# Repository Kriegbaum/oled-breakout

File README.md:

# oled-breakout
Breakout board for Crystalfontz 128x128 Oled display

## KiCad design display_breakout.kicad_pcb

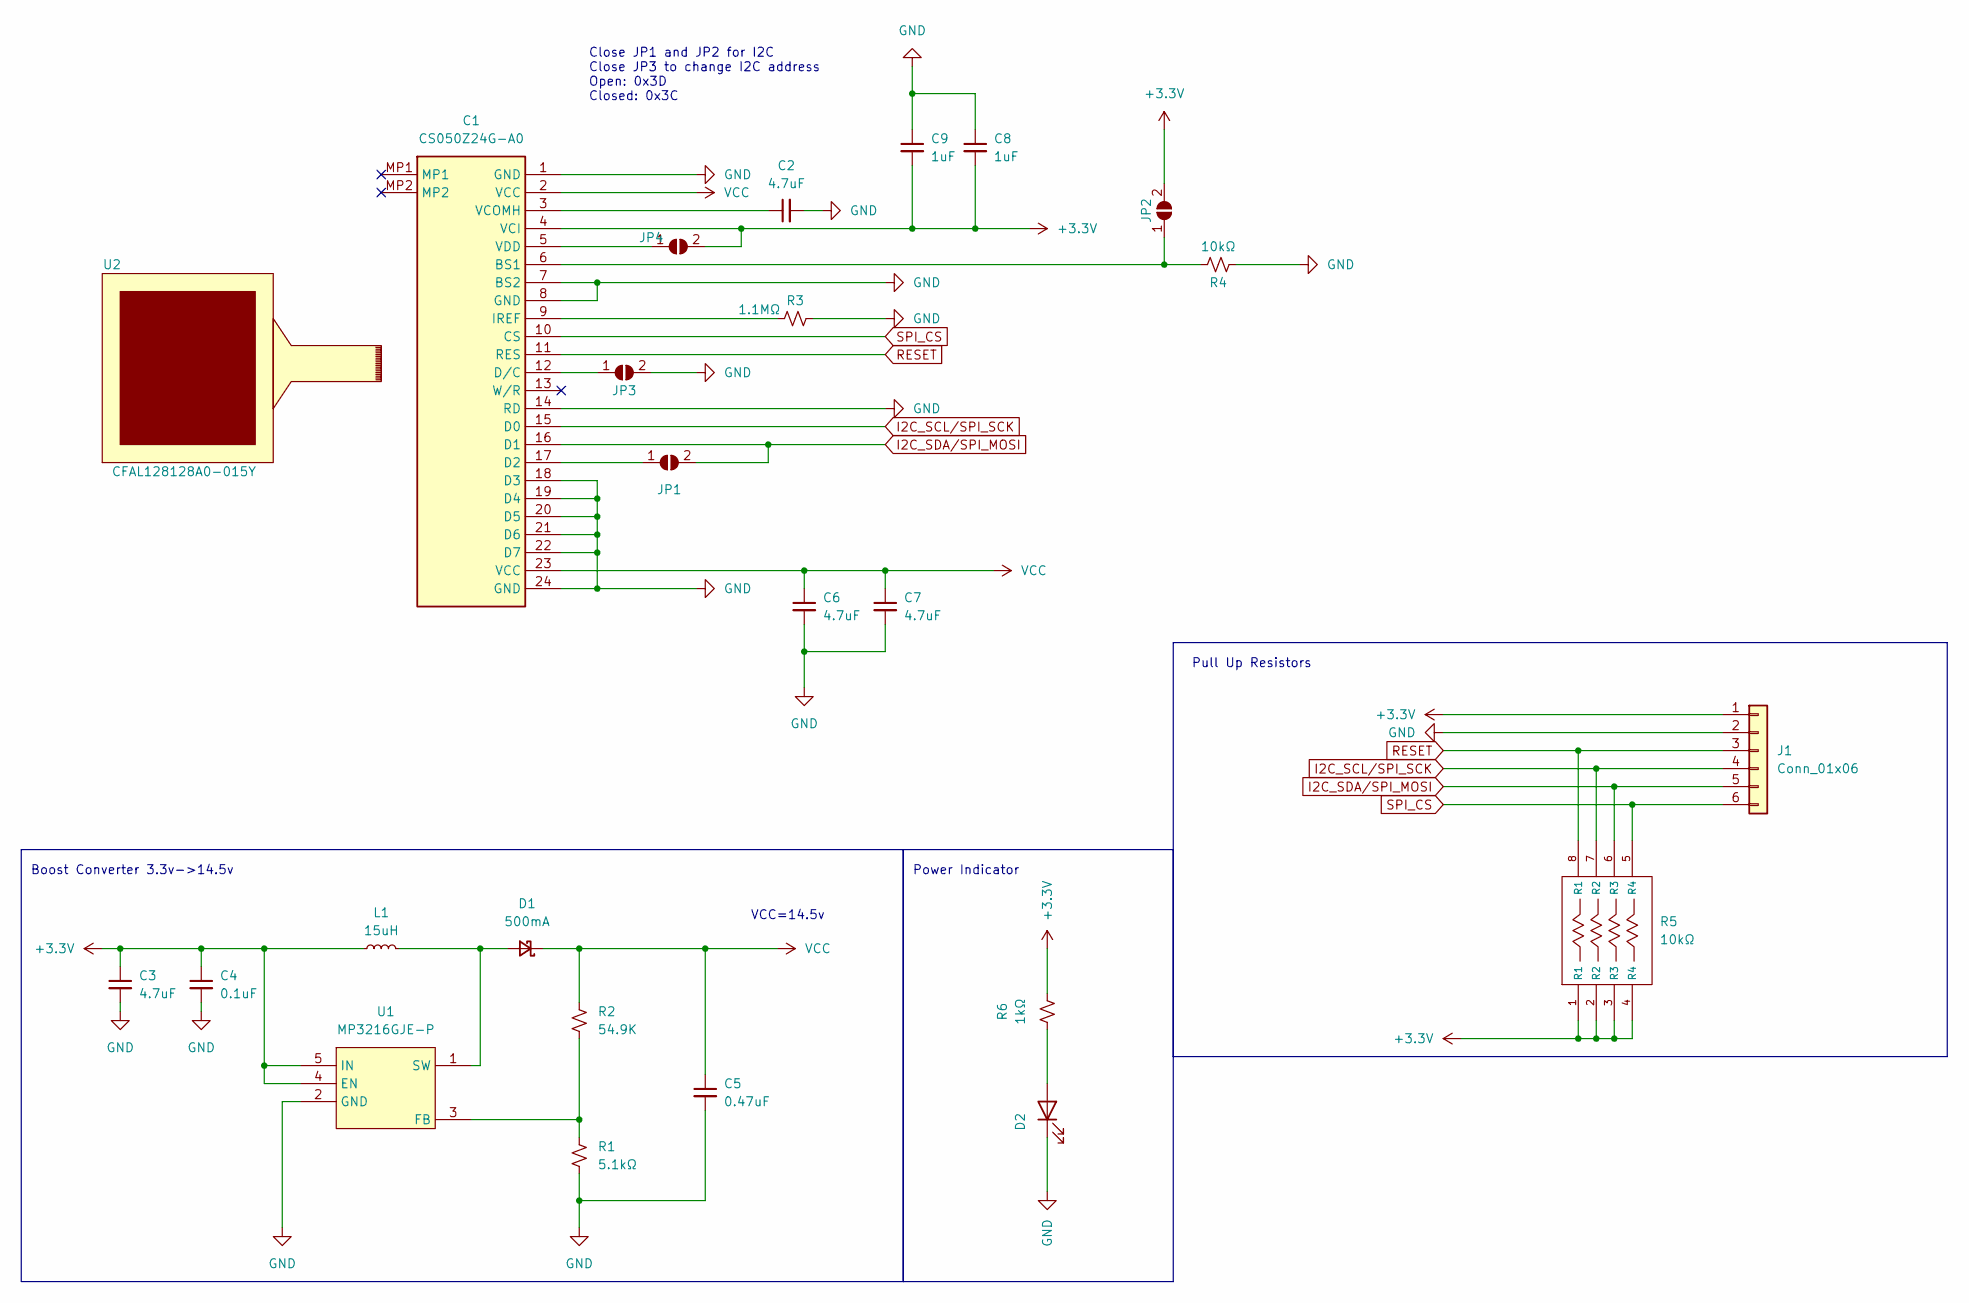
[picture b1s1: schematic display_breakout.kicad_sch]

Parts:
C1: CS050Z24G-A0; CS050Z24GA0; Manufacturer_Part_Number CS050Z24G-A0
C2, C3, C6, C7: CL21A475KAQNNNE; 0805_cap; Tolerance 10%; Voltage 25v
C4: CL21B104KBCNNNC; 0805_cap; Tolerance 10%; Voltage 50v
C5: UMK212B7474KG-T; 0805_cap; Tolerance 10%; Voltage 50v
C8, C9: CL21B105KBFNNNG; 0805_cap; Tolerance 10%; Voltage 50v
D1: B0540WS-TP; D_SOD-323_HandSoldering; Voltage 40V
D2: QBLP615-R; LED_1206_3216Metric_Pad1.42x1.75mm_HandSolder
J1: Conn_01x06; PinHeader_1x06_P2.54mm_Vertical
JP1, JP2, JP3, JP4: SolderJumper_2_Open; SolderJumper-2_P1.3mm_Open_RoundedPad1.0x1.5mm
L1: SDEM25201B-150MS; L_1008_2520Metric_Pad1.43x2.20mm_HandSolder
R1: RC0805FR-075K1L; R_0805_2012Metric_Pad1.20x1.40mm_HandSolder
R2: RC0805FR-0754K9L; R_0805_2012Metric_Pad1.20x1.40mm_HandSolder
R3: RC0805FR-071M1L; R_0805_2012Metric_Pad1.20x1.40mm_HandSolder
R4: RC0805JR-0710KL; R_0805_2012Metric_Pad1.20x1.40mm_HandSolder
R5: YC124-JR-0710KL; Resistor_Array_0805_x4
R6: RNCP0805FTD1K00; R_0805_2012Metric_Pad1.20x1.40mm_HandSolder
U1: MP3216GJE-P; SOT-23-5; Input voltage 2.5-6v; Output voltage 0-36v
U2: CFAL128128A0-015Y; CFAL128128A0-015

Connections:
+3.3V: C1.4 (VCI), C3.1, C4.1, C8.2, C9.2, J1.1, JP2.2 (B), JP4.2 (B), L1.1, R5.1 (R1), R5.2 (R2), R5.3 (R3), R5.4 (R4), R6.2, U1.4 (EN), U1.5 (IN)
GND: C1.1 (GND), C1.7 (BS2), C1.8 (GND), C1.14 (RD), C1.18 (D3), C1.19 (D4), C1.20 (D5), C1.21 (D6), C1.22 (D7), C1.24 (GND), C2.2, C3.2, C4.2, C5.2, C6.2, C7.2, C8.1, C9.1, D2.1 (K), J1.2, JP3.2 (B), R1.2, R3.2, R4.1, U1.2 (GND)
I2C_SCL/SPI_SCK: C1.15 (D0), J1.4, R5.7 (R2)
I2C_SDA/SPI_MOSI: C1.16 (D1), J1.5, JP1.2 (B), R5.6 (R3)
unnamed: C1.6 (BS1), JP2.1 (A), R4.2
unnamed: C1.17 (D2), JP1.1 (A)
unnamed: C1.12 (D/C), JP3.1 (A)
unnamed: C1.9 (IREF), R3.1
unnamed: C1.3 (VCOMH), C2.1
unnamed: C1.5 (VDD), JP4.1 (A)
unnamed: D1.2 (A), L1.2, U1.1 (SW)
unnamed: D2.2 (A), R6.1
unnamed: R1.1, R2.2, U1.3 (FB)
RESET: C1.11 (RES), J1.3, R5.8 (R1)
SPI_CS: C1.10 (CS), J1.6, R5.5 (R4)
VCC: C1.2 (VCC), C1.23 (VCC), C5.1, C6.1, C7.1, D1.1 (K), R2.1

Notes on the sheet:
Boost Converter 3.3v->14.5v
VCC=14.5v
Close JP1 and JP2 for I2C Close JP3 to change I2C address Open: 0x3D Closed: 0x3C
Pull Up Resistors
Power Indicator

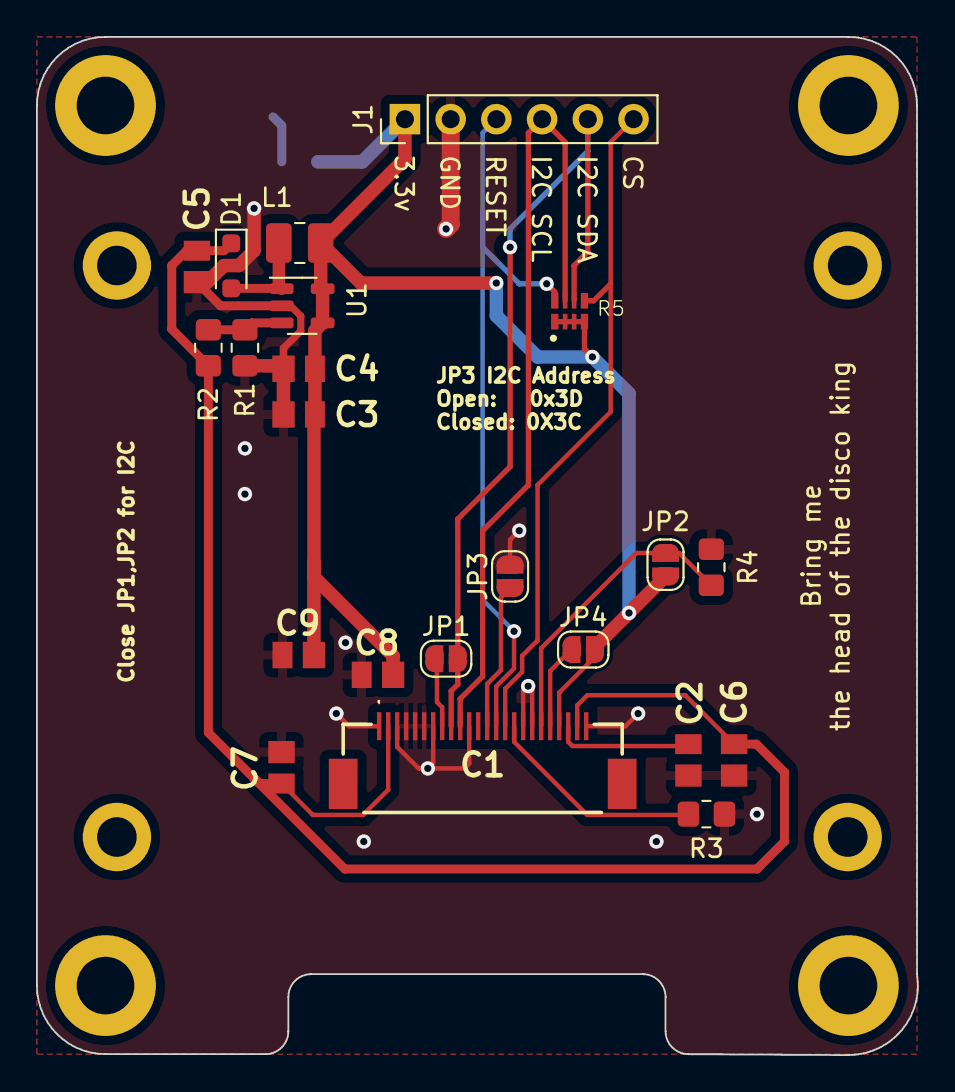
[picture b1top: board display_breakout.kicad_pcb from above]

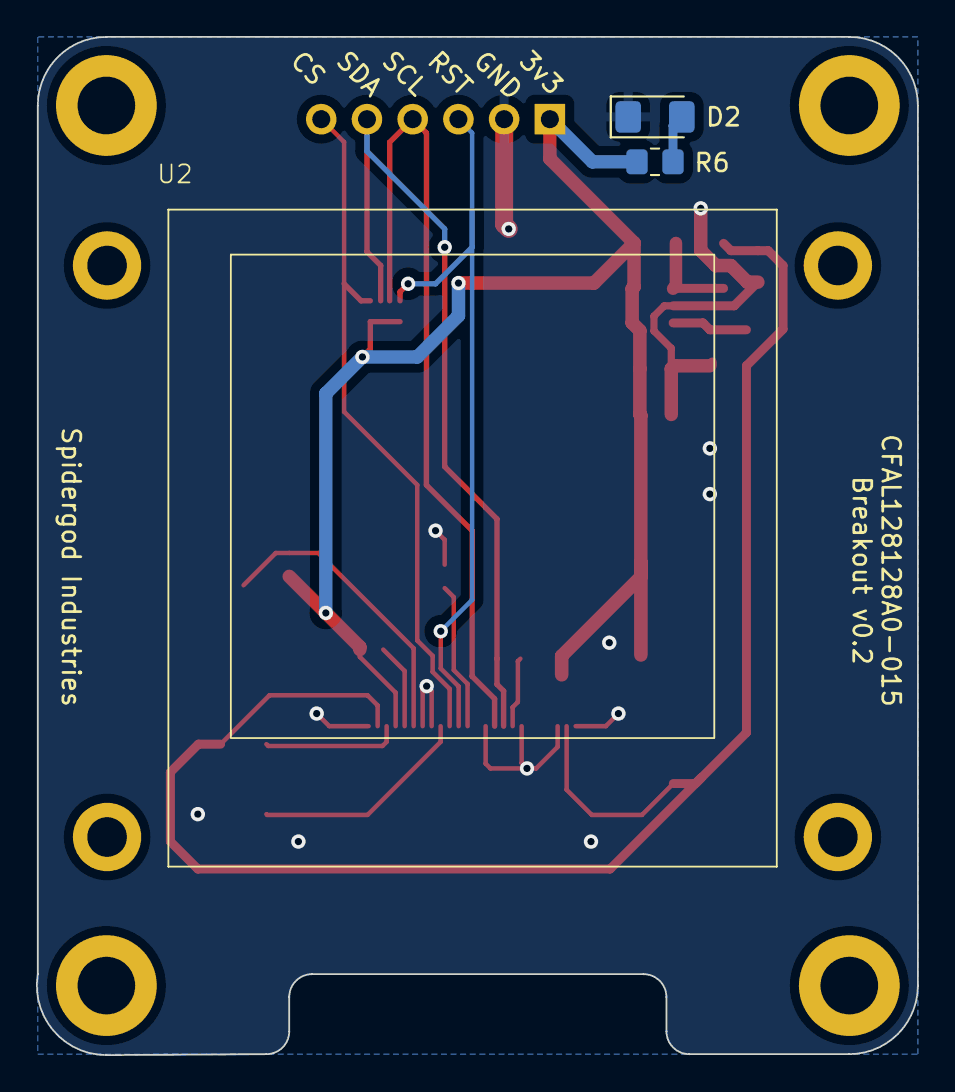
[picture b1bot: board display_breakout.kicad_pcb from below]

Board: 2 copper layers, 48.9 x 56.6 mm, 25 parts (3 on the bottom side), 16 nets.

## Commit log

2023-07-21 Fix backward display footprint, reroute everything
